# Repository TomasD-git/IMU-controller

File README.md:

# IMU controller  
### **Ultra low power IMU controller, can control anything over bluetooth using IMU, all running on coin cell CR2032 battery**  

## Features:  
- **Ultra low power 11.5uA power consumption in sleep mode**  
- **Most power consumption(LED on max brightness, cpu and ram fully active, BLE active, IMU running) 16.5mA**
- **Battery lasts 700ish days(11.1µA consumption on a 220mah battery)**
- **Powerfull BLE 5.3 with antenna**
- **NRF52810 as MCU**
- **BMI270 as IMU**
- **CR2032 battery**
- **Red LED**

<details>
<summary>How to does it work</summary>

## The button enables/disables the BLE  
## The LED indicates if BLE is active (LED flashes once = BLE on, LED flashes twice = BLE off)  
## All components are in deep sleep until accel detects movement  
## After few seconds of inactivity goes back to deep sleep  

</details>

<details>
<summary>How to flash</summary>

0. **Connect device to PC using segger j-link**   
1. **Open VS Code**  
2. **Select connected device in left bottom corner:** 

4. **Flash:**  

( For Debugging select: )  

</details>

<details>
<summary><strong>Power consumption</strong></summary>

## Deep Sleep:
| Component | What's active | Consumption |
|---|---|---|
| NRF52810 | Deep Sleep | 1.1µA |
| BMI270 | Accel-only Low power mode | 10µA |
| LED | Off | 0µA |
| Total | | 11.1µA |
| Battery life | 220,000µAh ÷ 11.1µA | ~825 days (~2.3 years) |
 
## Deep Sleep + slow BLE:
| Component | What's active | Consumption |
|---|---|---|
| NRF52810 | BLE with  4000ms interval (just to hold connections) | 6.4µA |
| BMI270 | Accel-only Low power mode | 10µA |
| LED | Off | 0µA |
| Total | | 16.4µA |
| Battery life | 220,000µAh ÷ 16.4µA | ~559 days (~1.53 years) |
 
## Fully active:
| Component | What's active | Consumption |
|---|---|---|
| NRF52810 | BLE with 7.5ms interval, CPU active | 13.8mA |
| BMI270 | Normal mode | 0.685mA |
| LED | On | 2.0mA |
| Total | | 16.485mA |
| Battery life | 220,000µAh ÷ 16.485mA | ~13.3 hours |

> **Can last less depending on quality of the Battery**  

</details>

<details>
<summary>How to Assemble</summary>

1. **Print all parts and assemble PCB**  
2. **Flash**  
3. **Place the Coin Cell battery into the holder**  
4. **Place the PCB inside the case**  
5. **Screw the bottom lid into the top one**  
6. **Verify it works by clicking the button**  

</details>

<details>  
<summary>Pictures</summary>  

</details>  

<details>
<summary>BOM</summary>

|Name          |Purpose                                       |Quantity  |Total Cost (USD)|Link                                                                                                                           |Distributor|
|--------------|----------------------------------------------|----------|----------------|-------------------------------------------------------------------------------------------------------------------------------|-----------|
|PCB + stencil |all components are on this                    |1         |13.97           |https://jlcpcb.com                                                                                                             |jlcpcb     |
|ALL components|all components that are on pcb                |1         |38.87           |https://lcsc.com                                                                                                               |lcsc       |
|CR2032        |battery which poweres the entire PCB          |1         |4               |                                                                                                                               |local store|
|SEGGER J-Link |Flashes the NRF board with firmware           |1         |4.94            |https://www.aliexpress.com/item/1005005802567589.html                                                                          |Aliexpress |
|EU tarrifs    |3 EU for each category for orders under 150 eu|3         |32.66           |https://commission.europa.eu/news-and-media/news/ensuring-fairness-and-safety-eur3-customs-duty-low-value-parcels-2026-06-29_en|EU         |
|              |                                              |Total cost|94.44           |                                                                                                                               |           |
|              |If outside EU                                 |Total cost|61.78           |                                                                                                                               |           |

</details>

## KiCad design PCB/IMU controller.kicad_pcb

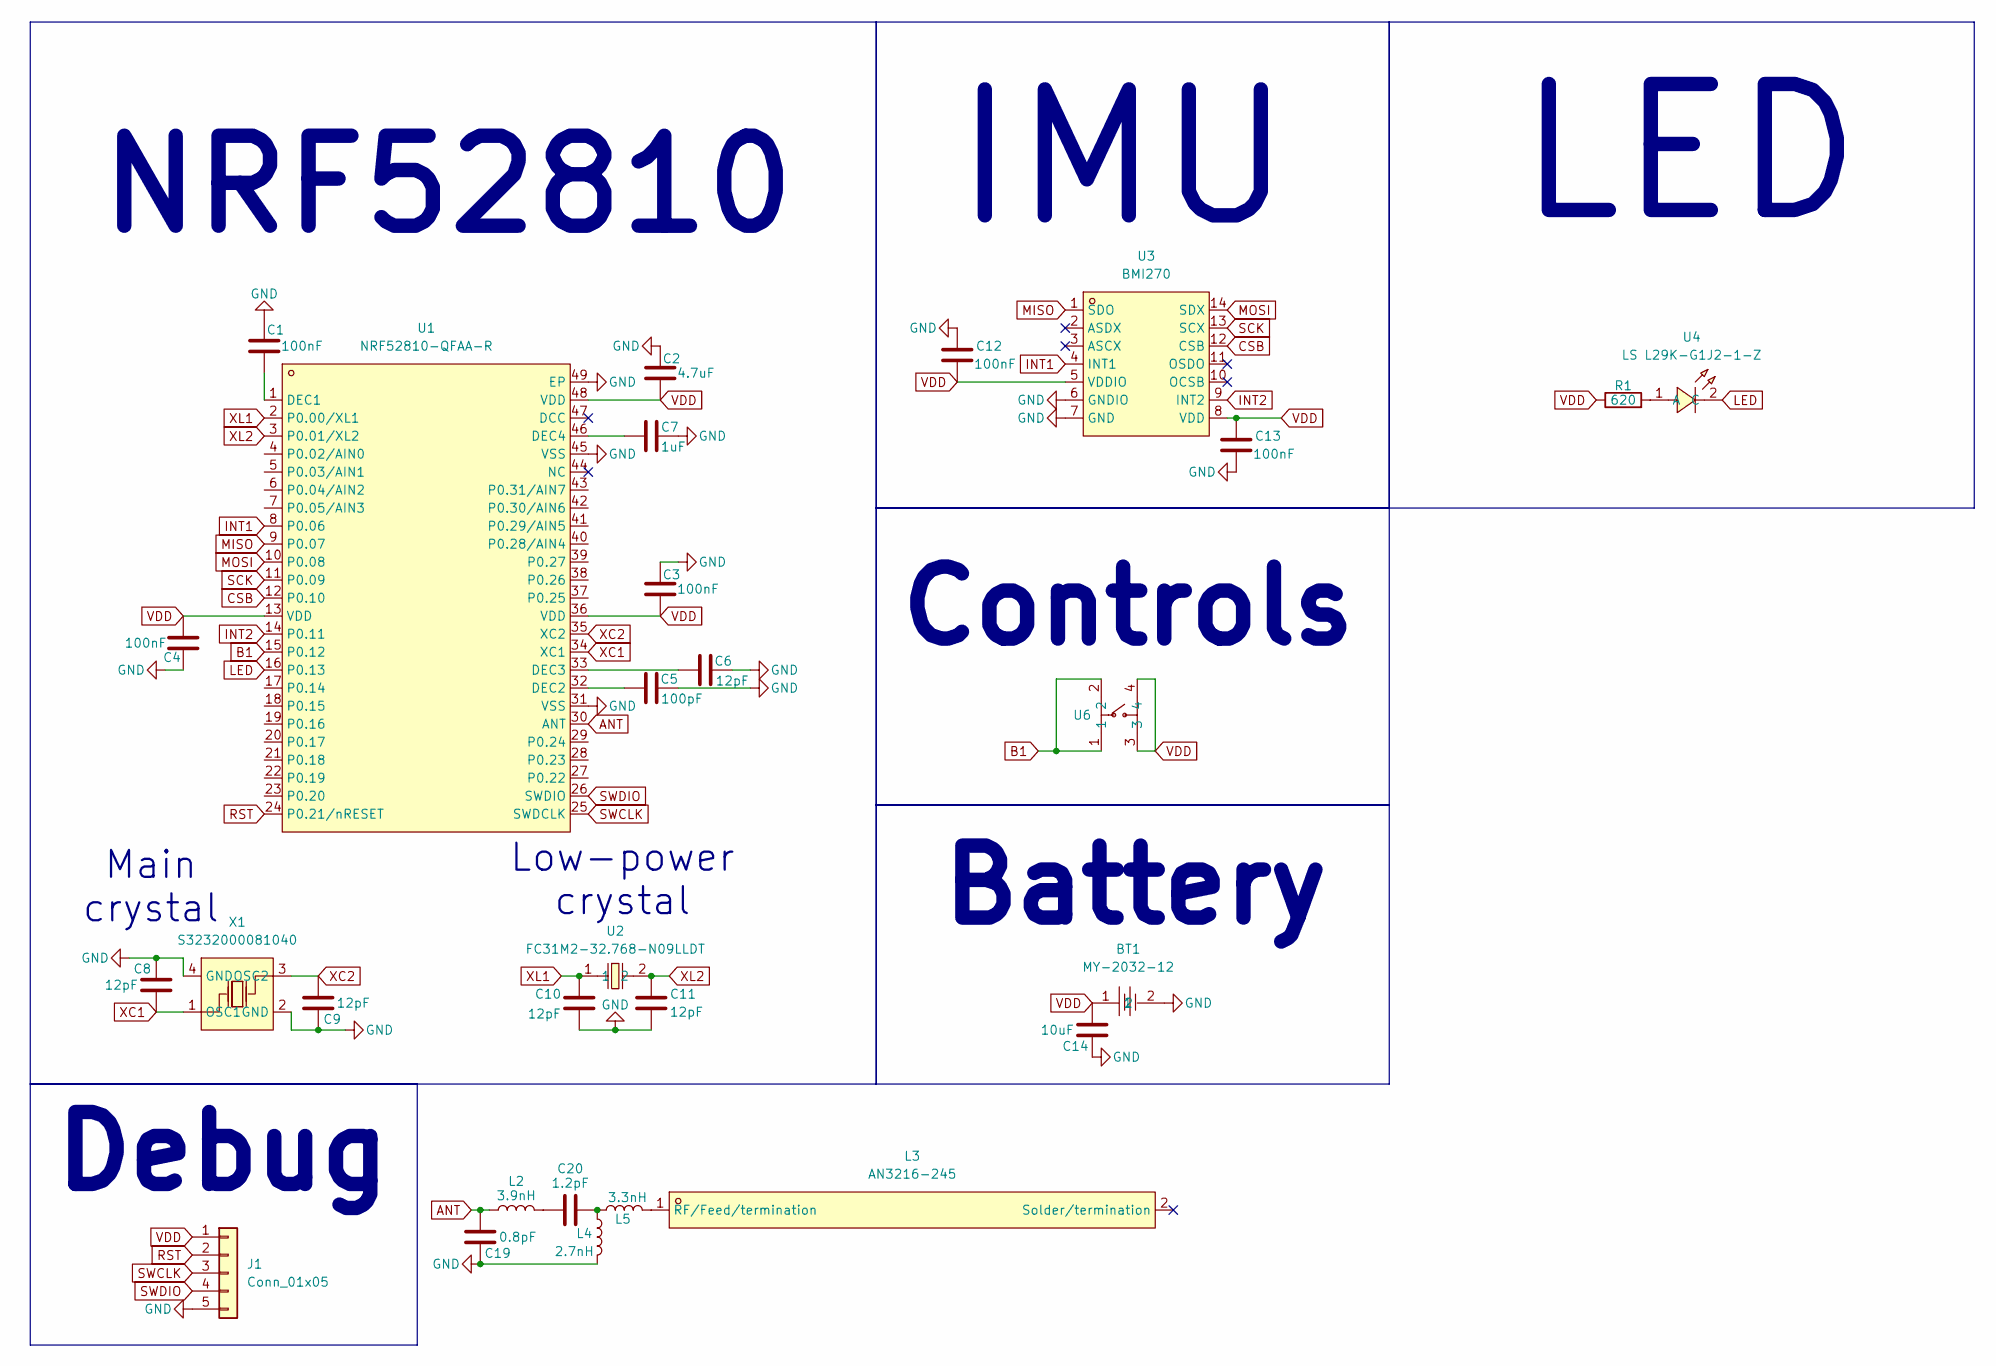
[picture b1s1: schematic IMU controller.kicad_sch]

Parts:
BT1: MY-2032-12; BAT-SMD_MY-2032-12; MPN MY-2032-12; LCSC Part C964833
C1, C3, C4, C12, C13: 100nF; C_0402_1005Metric
C2: 4.7uF; C_0603_1608Metric
C5: 100pF; C_0402_1005Metric
C6, C8, C9, C10, C11: 12pF; C_0402_1005Metric
C7: 1uF; C_0603_1608Metric
C14: 10uF; C_0805_2012Metric
C19: 0.8pF; C_0402_1005Metric
C20: 1.2pF; C_0402_1005Metric
J1: Conn_01x05; PinSocket_1x05_P2.00mm_Vertical
L2: 3.9nH; L_0402_1005Metric
L3: AN3216-245; ANT-SMD_L3.2-W1.6-A; MPN AN3216-245; LCSC Part C2916136
L4: 2.7nH; L_0402_1005Metric
L5: 3.3nH; L_0402_1005Metric
R1: 620; R_0603_1608Metric
U1: NRF52810-QFAA-R; UQFN-48_L6.0-W6.0-P0.40-BL-EP4.6; MPN NRF52810-QFAA-R; LCSC Part C141828
U2: FC31M2-32.768-N09LLDT; CRYSTAL-SMD_L3.2-W1.5; MPN FC31M2-32.768-N09LLDT; LCSC Part C2848222
U3: BMI270; LGA-14_L3.0-W2.5-P0.50-BR; MPN BMI270; LCSC Part C2836813
U4: LS L29K-G1J2-1-Z; LED-SMD_L1.3-W0.8-LS1.7-FD; MPN LS L29K-G1J2-1-Z; LCSC Part C7466002
U6: PTS526SMG15SMTR21 LFS; SW-SMD_4P-L4.8-W4.8-P3.70-LS6.4-1; MPN PTS526SMG15SMTR21 LFS; LCSC Part C6630024
X1: S3232000081040; CRYSTAL-SMD_4P-L3.2-W2.5-BL; MPN S3232000081040; LCSC Part C426985

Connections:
ANT: C19.1, L2.1, U1.30 (ANT)
B1: U1.15 (P0.12), U6.1, U6.2
CSB: U1.12 (P0.10), U3.12 (CSB)
GND: BT1.2, C1.1, C2.1, C3.1, C4.1, C5.2, C6.2, C7.1, C8.1, C9.1, C10.2, C11.2, C12.2, C13.1, C14.2, C19.2, J1.5, L4.2, U1.31 (VSS), U1.45 (VSS), U1.49 (EP), U3.6 (GNDIO), U3.7 (GND), X1.2 (GND), X1.4 (GND)
INT1: U1.8 (P0.06), U3.4 (INT1)
INT2: U1.14 (P0.11), U3.9 (INT2)
LED: U1.16 (P0.13), U4.2 (C)
MISO: U1.9 (P0.07), U3.1 (SDO)
MOSI: U1.10 (P0.08), U3.14 (SDX)
unnamed: C20.1, L2.2
unnamed: C20.2, L4.1, L5.1
unnamed: L3.1 (RF/Feed/termination), L5.2
unnamed: C1.2, U1.1 (DEC1)
unnamed: C5.1, U1.32 (DEC2)
unnamed: C6.1, U1.33 (DEC3)
unnamed: C7.2, U1.46 (DEC4)
unnamed: R1.2, U4.1 (A)
RST: J1.2, U1.24 (P0.21/nRESET)
SCK: U1.11 (P0.09), U3.13 (SCX)
SWCLK: J1.3, U1.25 (SWDCLK)
SWDIO: J1.4, U1.26 (SWDIO)
VDD: BT1.1, C2.2, C3.2, C4.2, C12.1, C13.2, C14.1, J1.1, R1.1, U1.13 (VDD), U1.36 (VDD), U1.48 (VDD), U3.5 (VDDIO), U3.8 (VDD), U6.3, U6.4
XC1: C8.2, U1.34 (XC1), X1.1 (OSC1)
XC2: C9.2, U1.35 (XC2), X1.3 (OSC2)
XL1: C10.1, U1.2 (P0.00/XL1), U2.1
XL2: C11.1, U1.3 (P0.01/XL2), U2.2

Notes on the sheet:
Battery
Low-power crystal
Controls
NRF52810
Main crystal
LED
IMU
Debug

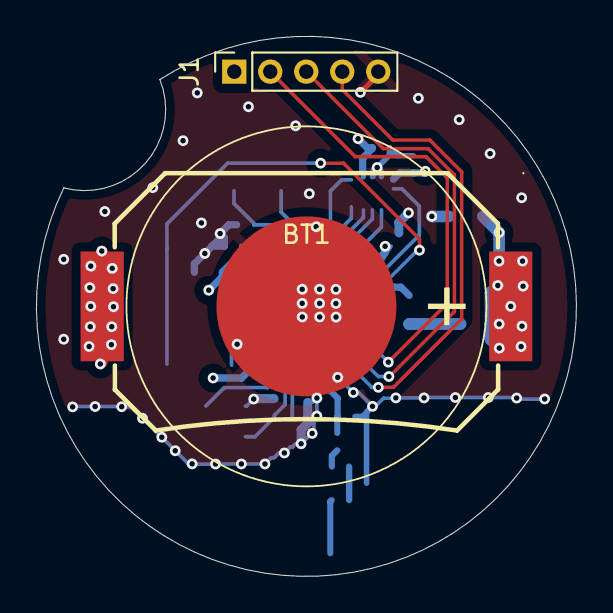
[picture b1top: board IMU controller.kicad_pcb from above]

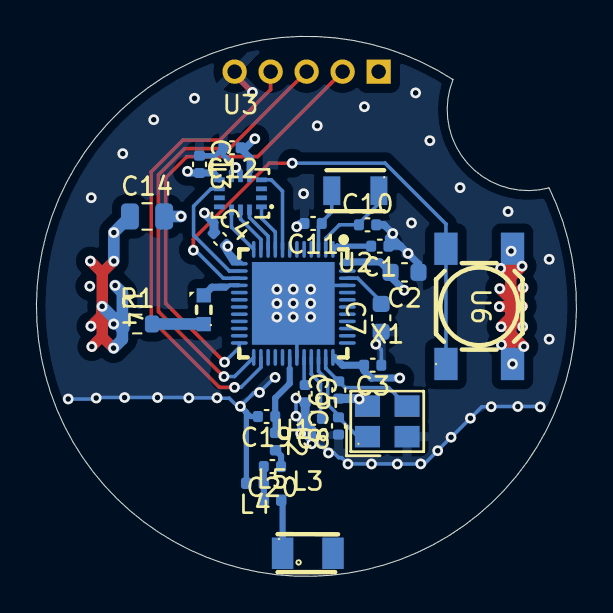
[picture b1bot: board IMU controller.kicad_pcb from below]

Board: 4 copper layers, 30.0 x 30.0 mm, 29 parts (27 on the bottom side), 26 nets.

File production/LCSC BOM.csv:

Designator,Footprint,Quantity,Value,LCSC Part #
BT1,BAT-SMD_MY-2032-12,1,MY-2032-12,C964833
"C1, C12, C13, C3, C4",402,5,100nF,C60474
"C10, C11, C6, C8, C9",402,5,12pF,C106201
C14,805,1,10uF,C15850
C19,402,1,0.8pF,C29936
C2,603,1,4.7uF,C88902
C20,402,1,1.2pF,C19666
C5,402,1,100pF,C1551
C7,603,1,1uF,C26409
J1,PinSocket_1x05_P2.00mm_Vertical,1,Conn_01x05,
L2,402,1,3.9nH,C98062
L3,ANT-SMD_L3.2-W1.6-A,1,AN3216-245,C2916136
L4,402,1,2.7nH,C91239
L5,402,1,3.3nH,C86064
R1,603,1,620,C137695
U1,UQFN-48_L6.0-W6.0-P0.40-BL-EP4.6,1,NRF52810-QFAA-R,C1558383
U2,CRYSTAL-SMD_L3.2-W1.5,1,FC31M2-32.768-N09LLDT,C2848222
U3,LGA-14_L3.0-W2.5-P0.50-BR,1,BMI270,C2836813
U4,LED-SMD_L1.3-W0.8-LS1.7-FD,1,LS L29K-G1J2-1-Z,C7466002
U6,SW-SMD_4P-L4.8-W4.8-P3.70-LS6.4-1,1,PTS526SMG15SMTR21 LFS,C6630024
X1,CRYSTAL-SMD_4P-L3.2-W2.5-BL,1,S3232000081040,C426985
